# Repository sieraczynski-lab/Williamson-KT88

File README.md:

# Williamson KT88

Lampowy wzmacniacz push-pull w klasycznej topologii Williamsona (wszystkie lampy sterujące na 6SN7), z końcówką na parze KT88 w układzie ultralinearnym (UL). Projekt to wzmacniacz **onyx1944** na jego płytce VA1523:

- wersja na KT88 (zdjęcia, PCB): https://onyx1944.wordpress.com/2023/11/21/williamson-kt88/
- wersja na 6S33S (schemat i zasilacz): https://onyx1944.wordpress.com/2020/03/16/6s33s-williamson-amplifier/

Płytka **VA1523-V1.0** jest kupiona od Onyxa (bez lamp i transformatorów), a Onyx udostępnił schematy. Schemat w tym repozytorium jest przerysowany z jego schematu i **poprawiony według wartości faktycznie wlutowanych na płytce**. Pomarańczowe elementy to te, które trzeba sprawdzić albo dobrać pod toroid TTG-KT88PP i własny transformator sieciowy. Oryginalnych plików Onyxa tu nie ma, to jego praca.

> **Status: płytka w ręku, przed uruchomieniem.** Punkty pracy są szacunkowe (model lampy, Ua ≈ 465 V), do potwierdzenia pomiarem.

> ⚠️ **Wysokie napięcie.** Ua ok. 465 V, a na zimno i przy wysokim napięciu sieci więcej. Kondensatory filtrów rozładowują się przez rezystory 560 k i dzielnik żarzenia; to trwa od kilkudziesięciu sekund do kilku minut. Przed dotknięciem płytki zawsze zmierz napięcie.

## Schematy

| Plik | Zawartość |
|---|---|
| [`schematy/kanal.svg`](schematy/kanal.svg) | Jeden kanał wg VA1523: 6SN7 (wejście + katodyna) → 6SN7 (driver) → 2× KT88 UL, bias osobno dla każdej lampy |
| [`schematy/zasilacz.svg`](schematy/zasilacz.svg) | Zasilacz z płytki (osobno w każdym kanale): mostek, CLC z dławikiem 10 H, Uaa przez R128, bias, podniesienie żarzenia |
| [`schematy/plytka_zasilacza.svg`](schematy/plytka_zasilacza.svg) | Własna płytka zasilacza: bezpieczniki, miękki start K1/K2, opóźnione anody K3/K4 z R_IN, napięcia przemienne do płytki Onyxa, pomiar Ua i dioda HV |
| [`bom/do_zamowienia.csv`](bom/do_zamowienia.csv) | Lista zakupów: zmiany na płytce Onyxa (rezystory 1 %, brakujące R136/R137, kondensatory wejściowe), gniazda, mechanika, przewody, transformatory |
| [`pcb/`](pcb/) | Płytki do zamówienia (KiCad 4 dla EasyEDA Standard, 5 dla EasyEDA Pro i KiCad 8, z klasami sieci): nowy zasilacz 100 × 100 mm, nowa płytka UL/trioda na oba kanały (4 przekaźniki, 100 × 66 mm) oraz z Soloista sterowanie ESP32, przełącznik kolumn, selektor. Połączenia: [`pcb/CZYTAJ_MNIE.txt`](pcb/CZYTAJ_MNIE.txt) |
| [`docs/soloist/`](docs/soloist/) | Opis sterowania i selektora (kopia z Soloista) |
| [`schematy/ul_trioda.svg`](schematy/ul_trioda.svg) | Okablowanie przełącznika UL / trioda: toroid, płytka UL, J101 Onyxa |
| [`schematy/williamson-kt88.html`](schematy/williamson-kt88.html) | Oba schematy z punktami pracy, różnicami płytka/schemat, listą zmian i uruchomieniem (otwórz w przeglądarce) |

## Najważniejsze dane

| | Wartość |
|---|---|
| Lampy | V1, V2: 6SN7 (6N8S); V5, V6: KT88 (lewy kanał; prawy V3, V4, V7, V8) |
| Front end | wejście ok. 4,3 mA / 95 V, katodyna 22k/22k ok. 4,5 mA, driver ok. 5 mA na triodę (bez balansu AC) |
| Końcówka | KT88 UL, Ua ≈ 465 V, 50–55 mA (0,50–0,55 V na 10 Ω), Ug1 ≈ −45…−55 V |
| Transformator wyjściowy | toroidy.pl **TTG-KT88PP** (u Onyxa Hammond 1650HA 6,6 kΩ) |
| Sprzężenie zwrotne | R129 15k z **odczepu 8 Ω** (ok. 12 dB), C123 niemontowany |
| Czułość / moc | ok. 0,65 V / ok. 40 W na kanał, kolumny na odczepie 4 Ω |
| Transformator sieciowy | 400 VA: 360 V (odczepy 345/375 V)/0,65 A, 58 V/100 mA, 6,3 V/8 A, 6,3 V/3 A, ekran ([docs/08](docs/08-zamowienie-toroidy.md)) |
| Dławiki | 2× 10 H / 250 mA / 45 Ω na L106 / L206 |

## Płytka a schemat Onyxa

| Element | Na schemacie | Na płytce |
|---|---|---|
| R117 / R217 | 220k / 1k | **100k / 100k** |
| R124 / R224 | 10 Ω / 470k | **10 Ω / 10 Ω** |
| C123 / C223 | 56 pF | **brak** |
| R101 | 1M | **220k** |
| R103 | 47k | **33k** |
| R104 / C102 | 47 Ω / 47 µF | **zwora / brak** |
| R111, R112 | 470k | **300k** |
| R119, R120 | 470k | **68k** |
| P101, P102 | 47k | **20k** |
| R139, R140 | 47k | **4k7** |
| R129 | 22k | **15k** |
| R134 | 10 Ω | **5,1 Ω** |
| R136 / R137 | 100k / 10k | **brak** w lewym, **300k / 68k** w prawym |
| R130–R133 | 330 Ω | **390 Ω** |
| R143–R152 | 680k | **560k** |
| R125, R126 | 100 Ω | **150 Ω** |
| R141, R142 | 10 Ω / 100 Ω | **47 Ω / 47 Ω** |

## Zasilacz, sterowanie, dodatki i obudowa

Płytka Onyxa dostaje własną, prostą płytkę zasilacza (bez prostowników i filtrów, bo te są na płytce Onyxa): miękki start, opóźnione anody, pomiar Ua. Z [Soloist-KT88](https://github.com/sieraczynski-lab/Soloist-KT88) bierze sterownik ESP32 z automatyczną korektą biasu, układ przełącznika UL / trioda (tu jedna płytka na oba kanały), przełącznik kolumn z triggerem, selektor z drabinką głośności i obudowę. Te płytki Soloista bez zmian w PCB, płytka Onyxa bez cięcia ścieżek. Szczegóły: [docs/09-integracja-soloist.md](docs/09-integracja-soloist.md), obudowa: [`obudowa/`](obudowa/).

## Decyzje i otwarte sprawy

- **Toroid TTG-KT88PP** zamiast Hammonda: sprzężenie zwrotne z odczepu 8 Ω (zbliżona głębokość pętli jak u Onyxa), kolumny na 4 Ω. Kompensację C123 dobrać na oscyloskopie, jeśli prostokąt dzwoni.
- **R128 / R228** (4k7) dobrać do własnego Ua, żeby Uaa wyszło ok. 380–420 V.
- **Driver bez balansu AC:** do V2 dawać 6SN7 o zbliżonych prądach obu triod.
- **Dodatek:** rezystor 100 Ω / 2 W między 4 Ω a COM (wzmacniacz nie pracuje bez obciążenia).
- **Odpowiedzi Onyxa (12.11.2026):** u niego TR1 to toroidy.pl TSTA-0300/001 (300 VA), radzi większy, więc 400 VA jest w porządku. Sprzężenie zwrotne z odczepu 8 Ω (zgodnie z planem). C123 i ewentualnie R102/C101 tylko pod prostokąt (u niego niepotrzebne). Pomyłki na schemacie potwierdzone. Szczegóły w [docs/07](docs/07-wersje-onyxa.md#odpowiedzi-onyxa-12112026).
- **Sprawdzone:** sieć UaFF-L2 (środek żarzenia KT88) to masa (wspólny punkt C108, C126, R142).
- Projekt równoległy: [Soloist-KT88](https://github.com/sieraczynski-lab/Soloist-KT88) (Mullard: EF86 + E88CC LTP + KT88), z podobnym transformatorem sieciowym i tymi samymi toroidami.

## Notatki

1. [Lampy KT88 Psvane: serie i różnice](docs/01-lampy-kt88.md)
2. [Transformatory wyjściowe: Hammond, toroidy.pl, Ogonowski](docs/02-transformatory-wyjsciowe.md)
3. [Topologia: Williamson, Mullard 5-20, 6S33S, 6SN7](docs/03-topologia.md)
4. [Kolumny: impedancja, zwrotnica 2,5-drożna, spadek bafla](docs/04-kolumny.md)
5. [Uruchomienie krok po kroku](docs/05-uruchomienie.md)
6. [Zamawianie płytek PCB](docs/06-pcb.md)
7. [Wersje Onyxa: zdjęcia, schemat i płytka VA1523](docs/07-wersje-onyxa.md)
8. [Specyfikacja do zamówienia w toroidy.pl](docs/08-zamowienie-toroidy.md)
9. [Zasilacz, sterowanie, dodatki i obudowa](docs/09-integracja-soloist.md)
10. [Oprogramowanie ESP32: założenia](docs/10-oprogramowanie-esp32.md)

## Generowanie schematów

Schematy są rysowane skryptem (Python 3, bez dodatkowych bibliotek):

```bash
python3 narzedzia/build.py
```

Obudowa (STEP, DXF, widoki) powstaje z `python3 narzedzia/obudowa/export.py` (wymaga `numpy` i `matplotlib`).

Skrypt [`narzedzia/gen_schemat.py`](narzedzia/gen_schemat.py) zawiera geometrię i wartości elementów. Po zmianie wartości wystarczy uruchomić `build.py` ponownie, a SVG i strona HTML w `schematy/` zostaną odświeżone.

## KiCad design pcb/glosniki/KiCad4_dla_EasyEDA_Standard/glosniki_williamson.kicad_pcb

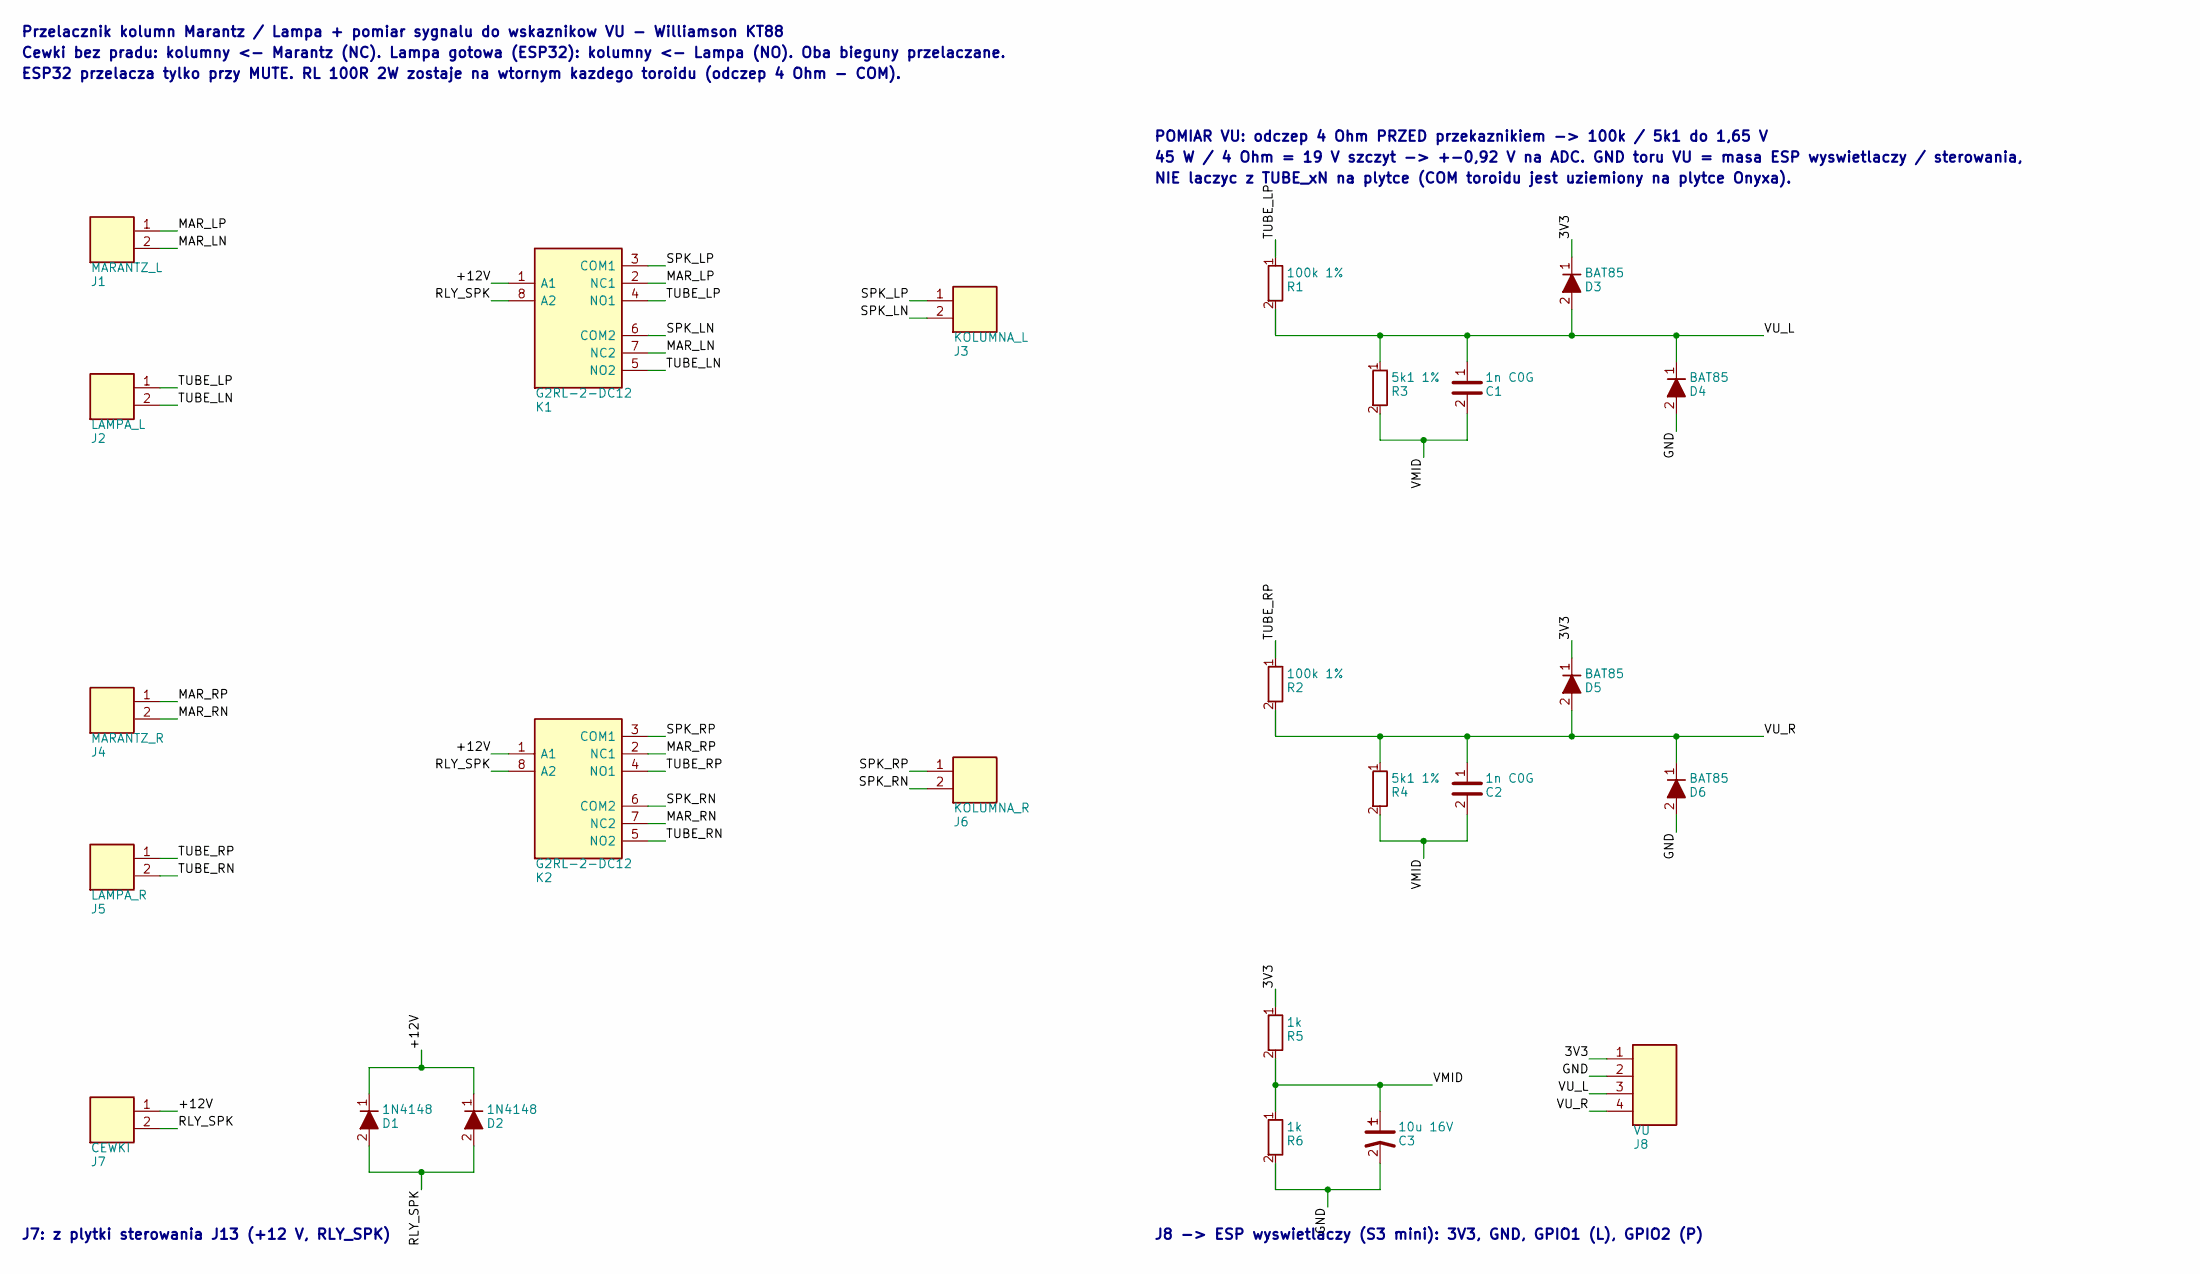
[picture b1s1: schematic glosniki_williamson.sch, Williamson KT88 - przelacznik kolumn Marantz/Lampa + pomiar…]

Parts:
C1, C2: 1n C0G; C_Box_P5_7x4
C3: 10u 16V; CP_Radial_D6.3_P2.5
D1, D2: 1N4148; D_DO-35_P7.62
D3, D4, D5, D6: BAT85; D_DO-35_P7.62_V
J1: MARANTZ_L; TerminalBlock_1x02_P5.08
J2: LAMPA_L; TerminalBlock_1x02_P5.08
J3: KOLUMNA_L; TerminalBlock_1x02_P5.08
J4: MARANTZ_R; TerminalBlock_1x02_P5.08
J5: LAMPA_R; TerminalBlock_1x02_P5.08
J6: KOLUMNA_R; TerminalBlock_1x02_P5.08
J7: CEWKI; PinHeader_1x02_P2.54
J8: VU; PinHeader_1x04_P2.54_H
K1, K2: G2RL-2-DC12; Relay_DPDT_Omron_G2RL
R1, R2: 100k 1%; R_Axial_0.5W_P12.7
R3, R4: 5k1 1%; R_Axial_0.5W_P12.7
R5, R6: 1k; R_Axial_0.5W_P12.7_V

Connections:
3V3: D3.1 (K), D5.1 (K), J8.1, R5.1
+12V: D1.1 (K), D2.1 (K), J7.1, K1.1 (A1), K2.1 (A1)
GND: C3.2, D4.2 (A), D6.2 (A), J8.2, R6.2
MAR_LN: J1.2, K1.7 (NC2)
MAR_LP: J1.1, K1.2 (NC1)
MAR_RN: J4.2, K2.7 (NC2)
MAR_RP: J4.1, K2.2 (NC1)
RLY_SPK: D1.2 (A), D2.2 (A), J7.2, K1.8 (A2), K2.8 (A2)
SPK_LN: J3.2, K1.6 (COM2)
SPK_LP: J3.1, K1.3 (COM1)
SPK_RN: J6.2, K2.6 (COM2)
SPK_RP: J6.1, K2.3 (COM1)
TUBE_LN: J2.2, K1.5 (NO2)
TUBE_LP: J2.1, K1.4 (NO1), R1.1
TUBE_RN: J5.2, K2.5 (NO2)
TUBE_RP: J5.1, K2.4 (NO1), R2.1
VMID: C1.2, C2.2, C3.1, R3.2, R4.2, R5.2, R6.1
VU_L: C1.1, D3.2 (A), D4.1 (K), J8.3, R1.2, R3.1
VU_R: C2.1, D5.2 (A), D6.1 (K), J8.4, R2.2, R4.1

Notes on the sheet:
Przelacznik kolumn Marantz / Lampa + pomiar sygnalu do wskaznikow VU - Williamson KT88
Cewki bez pradu: kolumny <- Marantz (NC). Lampa gotowa (ESP32): kolumny <- Lampa (NO). Oba bieguny przelaczane.
ESP32 przelacza tylko przy MUTE. RL 100R 2W zostaje na wtornym kazdego toroidu (odczep 4 Ohm - COM).
POMIAR VU: odczep 4 Ohm PRZED przekaznikiem -> 100k / 5k1 do 1,65 V
45 W / 4 Ohm = 19 V szczyt -> +-0,92 V na ADC. GND toru VU = masa ESP wyswietlaczy / sterowania,
NIE laczyc z TUBE_xN na plytce (COM toroidu jest uziemiony na plytce Onyxa).
J8 -> ESP wyswietlaczy (S3 mini): 3V3, GND, GPIO1 (L), GPIO2 (P)
J7: z plytki sterowania J13 (+12 V, RLY_SPK)

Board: 2 copper layers, 28 parts (0 on the bottom side), 19 nets, no tracks yet.

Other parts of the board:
MH1, MH2, MH3: M3; MountingHole_M3

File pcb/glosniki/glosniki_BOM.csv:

Oznaczenie;Wartosc;Footprint;Strona;X [mm];Y [mm];Grupa;LCSC;Uwagi
K1;G2RL-2-DC12;Relay_DPDT_Omron_G2RL;GORA;30.00;28.00;PRZEKAZNIKI GLOSNIKOW;C61458;"kanal L: bez pradu cewki kolumna <- Marantz (NC), cewka zasilona: kolumna <- Lampa (NO); + i - przelaczane"
K2;G2RL-2-DC12;Relay_DPDT_Omron_G2RL;GORA;72.00;28.00;PRZEKAZNIKI GLOSNIKOW;C61458;"kanal R: bez pradu cewki kolumna <- Marantz (NC), cewka zasilona: kolumna <- Lampa (NO); + i - przelaczane"
D1;1N4148;D_DO-35_P7.62;GORA;13.00;38.00;PRZEKAZNIKI GLOSNIKOW;;dioda cewki K1
D2;1N4148;D_DO-35_P7.62;GORA;62.00;38.50;PRZEKAZNIKI GLOSNIKOW;;dioda cewki K2
J1;MARANTZ_L;TerminalBlock_1x02_P5.08;GORA;12.00;5.00;ZLACZA;;z wyjscia glosnikowego Marantza, kanal L: 1 +, 2 -
J2;LAMPA_L;TerminalBlock_1x02_P5.08;GORA;27.00;5.00;ZLACZA;;z wtornego T101: 1 odczep 4 Ohm, 2 COM (masa Lampy)
J3;KOLUMNA_L;TerminalBlock_1x02_P5.08;GORA;42.00;5.00;ZLACZA;;do zaciskow kolumny L na tylnej sciance: 1 +, 2 -
J4;MARANTZ_R;TerminalBlock_1x02_P5.08;GORA;58.00;5.00;ZLACZA;;z Marantza, kanal R
J5;LAMPA_R;TerminalBlock_1x02_P5.08;GORA;73.00;5.00;ZLACZA;;z wtornego T201: 1 odczep 4 Ohm, 2 COM
J6;KOLUMNA_R;TerminalBlock_1x02_P5.08;GORA;88.00;5.00;ZLACZA;;do zaciskow kolumny R
J7;CEWKI;PinHeader_1x02_P2.54;GORA;95.50;36.00;ZLACZA;;z plytki sterowania J13
MH1;M3;MountingHole_M3;GORA;4.50;37.50;OTWORY;;
MH2;M3;MountingHole_M3;GORA;51.00;37.50;OTWORY;;
MH3;M3;MountingHole_M3;GORA;95.50;22.00;OTWORY;;

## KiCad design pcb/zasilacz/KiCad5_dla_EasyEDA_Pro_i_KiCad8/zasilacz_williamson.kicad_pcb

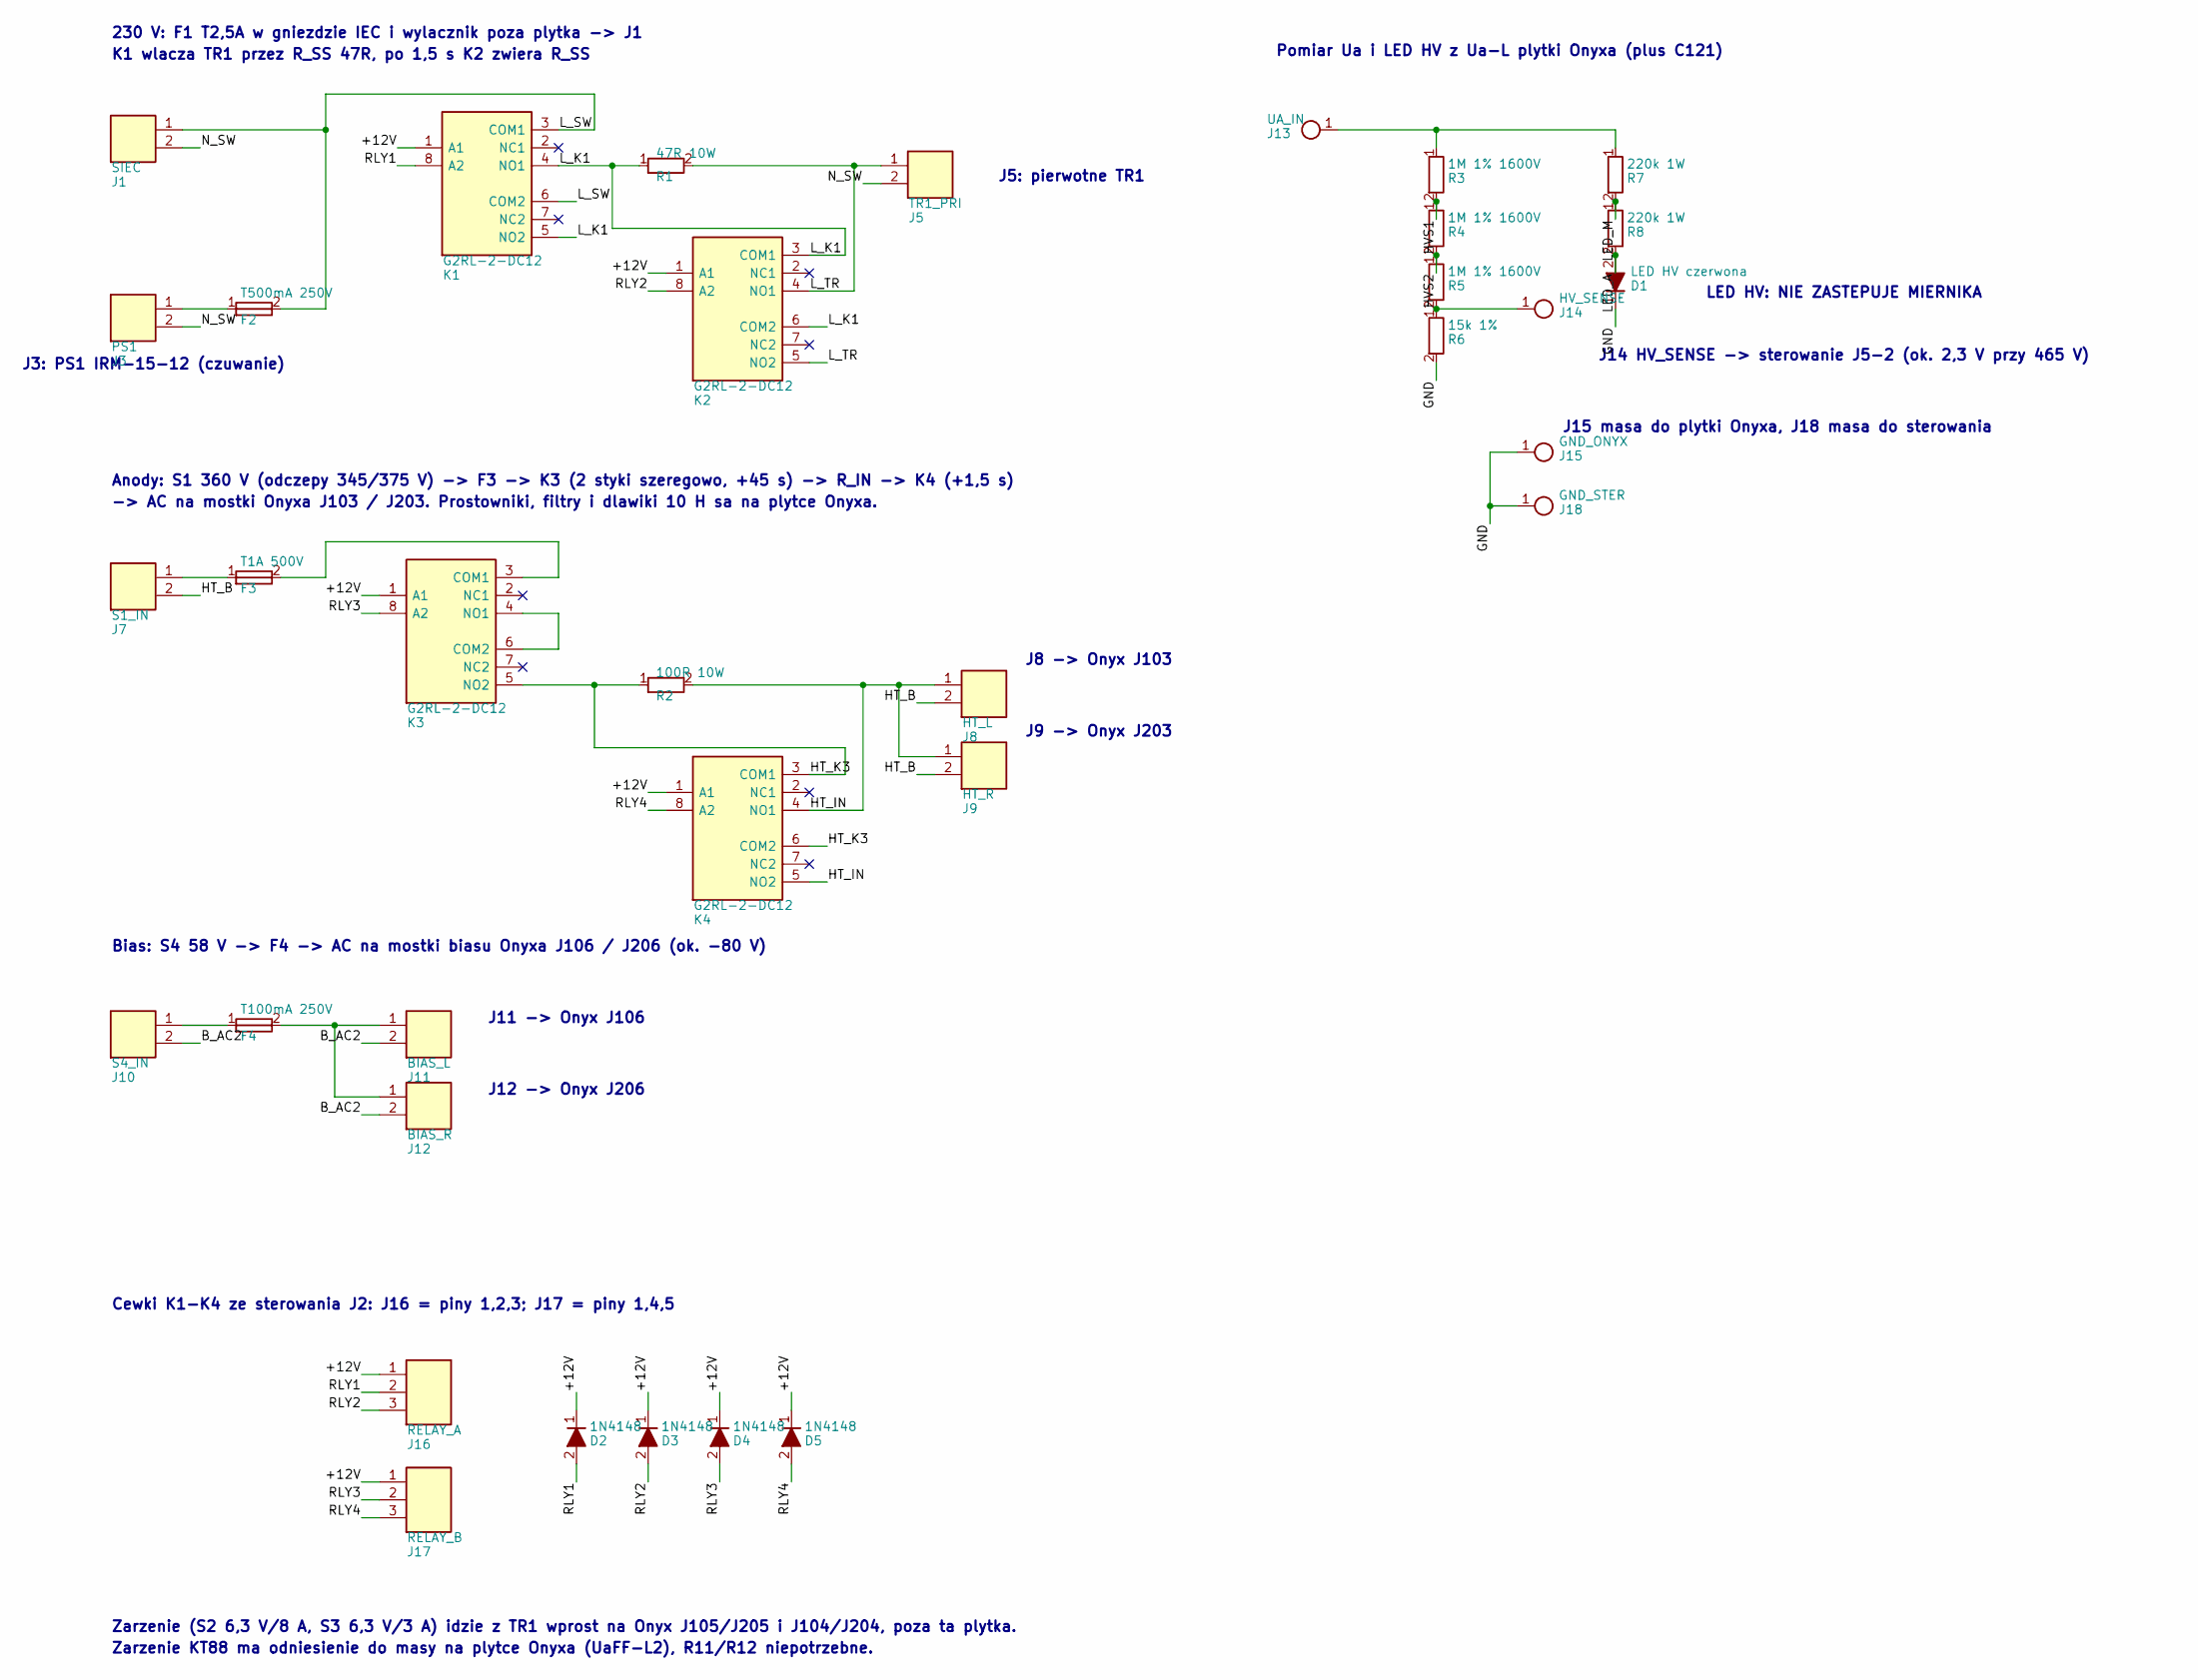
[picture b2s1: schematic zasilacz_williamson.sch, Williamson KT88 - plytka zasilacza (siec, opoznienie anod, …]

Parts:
D1: LED HV czerwona; LED_D3.0_P2.54
D2, D3, D4, D5: 1N4148; D_DO-35_P7.62_V
F2: T500mA 250V; Fuseholder_5x20_Closed_P22.5
F3: T1A 500V; Fuseholder_5x20_Closed_P22.5_V
F4: T100mA 250V; Fuseholder_5x20_Closed_P22.5
J1: SIEC; TerminalBlock_1x02_P5.08_V
J3: PS1; TerminalBlock_1x02_P5.08_V
J5: TR1_PRI; TerminalBlock_1x02_P5.08_V
J7: S1_IN; TerminalBlock_1x02_P7.62_V
J8: HT_L; TerminalBlock_1x02_P7.62_V
J9: HT_R; TerminalBlock_1x02_P7.62_V
J10: S4_IN; TerminalBlock_1x02_P5.08_V
J11: BIAS_L; TerminalBlock_1x02_P5.08
J12: BIAS_R; TerminalBlock_1x02_P5.08
J13: UA_IN; WirePad_4.5
J14: HV_SENSE; WirePad_3.5
J15: GND_ONYX; WirePad_4.5
J16: RELAY_A; PinHeader_1x03_P2.54
J17: RELAY_B; PinHeader_1x03_P2.54
J18: GND_STER; WirePad_3.5
K1, K2, K3, K4: G2RL-2-DC12; Relay_DPDT_Omron_G2RL
R1: 47R 10W; R_Cement_10W_P55.88_V
R2: 100R 10W; R_Cement_10W_P55.88_V
R3, R4, R5: 1M 1% 1600V; R_Axial_1W_P15.24_V
R6: 15k 1%; R_Axial_0.5W_P12.7_V
R7, R8: 220k 1W; R_Axial_1W_P15.24_V

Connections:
+12V: D2.1 (K), D3.1 (K), D4.1 (K), D5.1 (K), J16.1, J17.1, K1.1 (A1), K2.1 (A1), K3.1 (A1), K4.1 (A1)
B_AC1: F4.1, J10.1
B_AC2: J10.2, J11.2, J12.2
B_F: F4.2, J11.1, J12.1
GND: D1.1 (K), J15.1, J18.1, R6.2
HT_B: J7.2, J8.2, J9.2
HT_F: F3.2, K3.3 (COM1)
HT_IN: J8.1, J9.1, K4.4 (NO1), K4.5 (NO2), R2.2
HT_K3: K3.5 (NO2), K4.3 (COM1), K4.6 (COM2), R2.1
HT_TR: F3.1, J7.1
HVS1: R3.2, R4.1
HVS2: R4.2, R5.1
HV_SENSE: J14.1, R5.2, R6.1
K3_MID: K3.4 (NO1), K3.6 (COM2)
LED_A: D1.2 (A), R8.2
LED_M: R7.2, R8.1
L_K1: K1.4 (NO1), K1.5 (NO2), K2.3 (COM1), K2.6 (COM2), R1.1
L_SW: F2.2, J1.1, K1.3 (COM1), K1.6 (COM2)
L_TR: J5.1, K2.4 (NO1), K2.5 (NO2), R1.2
L_TR2: F2.1, J3.1
N_SW: J1.2, J3.2, J5.2
RLY1: D2.2 (A), J16.2, K1.8 (A2)
RLY2: D3.2 (A), J16.3, K2.8 (A2)
RLY3: D4.2 (A), J17.2, K3.8 (A2)
RLY4: D5.2 (A), J17.3, K4.8 (A2)
UA: J13.1, R3.1, R7.1

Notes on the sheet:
230 V: F1 T2,5A w gniezdzie IEC i wylacznik poza plytka -> J1
K1 wlacza TR1 przez R_SS 47R, po 1,5 s K2 zwiera R_SS
J5: pierwotne TR1
J3: PS1 IRM-15-12 (czuwanie)
Anody: S1 360 V (odczepy 345/375 V) -> F3 -> K3 (2 styki szeregowo, +45 s) -> R_IN -> K4 (+1,5 s)
-> AC na mostki Onyxa J103 / J203. Prostowniki, filtry i dlawiki 10 H sa na plytce Onyxa.
J8 -> Onyx J103
J9 -> Onyx J203
Bias: S4 58 V -> F4 -> AC na mostki biasu Onyxa J106 / J206 (ok. -80 V)
J11 -> Onyx J106
J12 -> Onyx J206
Pomiar Ua i LED HV z Ua-L plytki Onyxa (plus C121)
J14 HV_SENSE -> sterowanie J5-2 (ok. 2,3 V przy 465 V)
J15 masa do plytki Onyxa, J18 masa do sterowania
LED HV: NIE ZASTEPUJE MIERNIKA
Cewki K1-K4 ze sterowania J2: J16 = piny 1,2,3; J17 = piny 1,4,5
Zarzenie (S2 6,3 V/8 A, S3 6,3 V/3 A) idzie z TR1 wprost na Onyx J105/J205 i J104/J204, poza ta plytka.
Zarzenie KT88 ma odniesienie do masy na plytce Onyxa (UaFF-L2), R11/R12 niepotrzebne.

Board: 2 copper layers, 39 parts (0 on the bottom side), 26 nets, no tracks yet.

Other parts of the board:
MH1, MH2, MH3, MH4: M3; MountingHole_M3

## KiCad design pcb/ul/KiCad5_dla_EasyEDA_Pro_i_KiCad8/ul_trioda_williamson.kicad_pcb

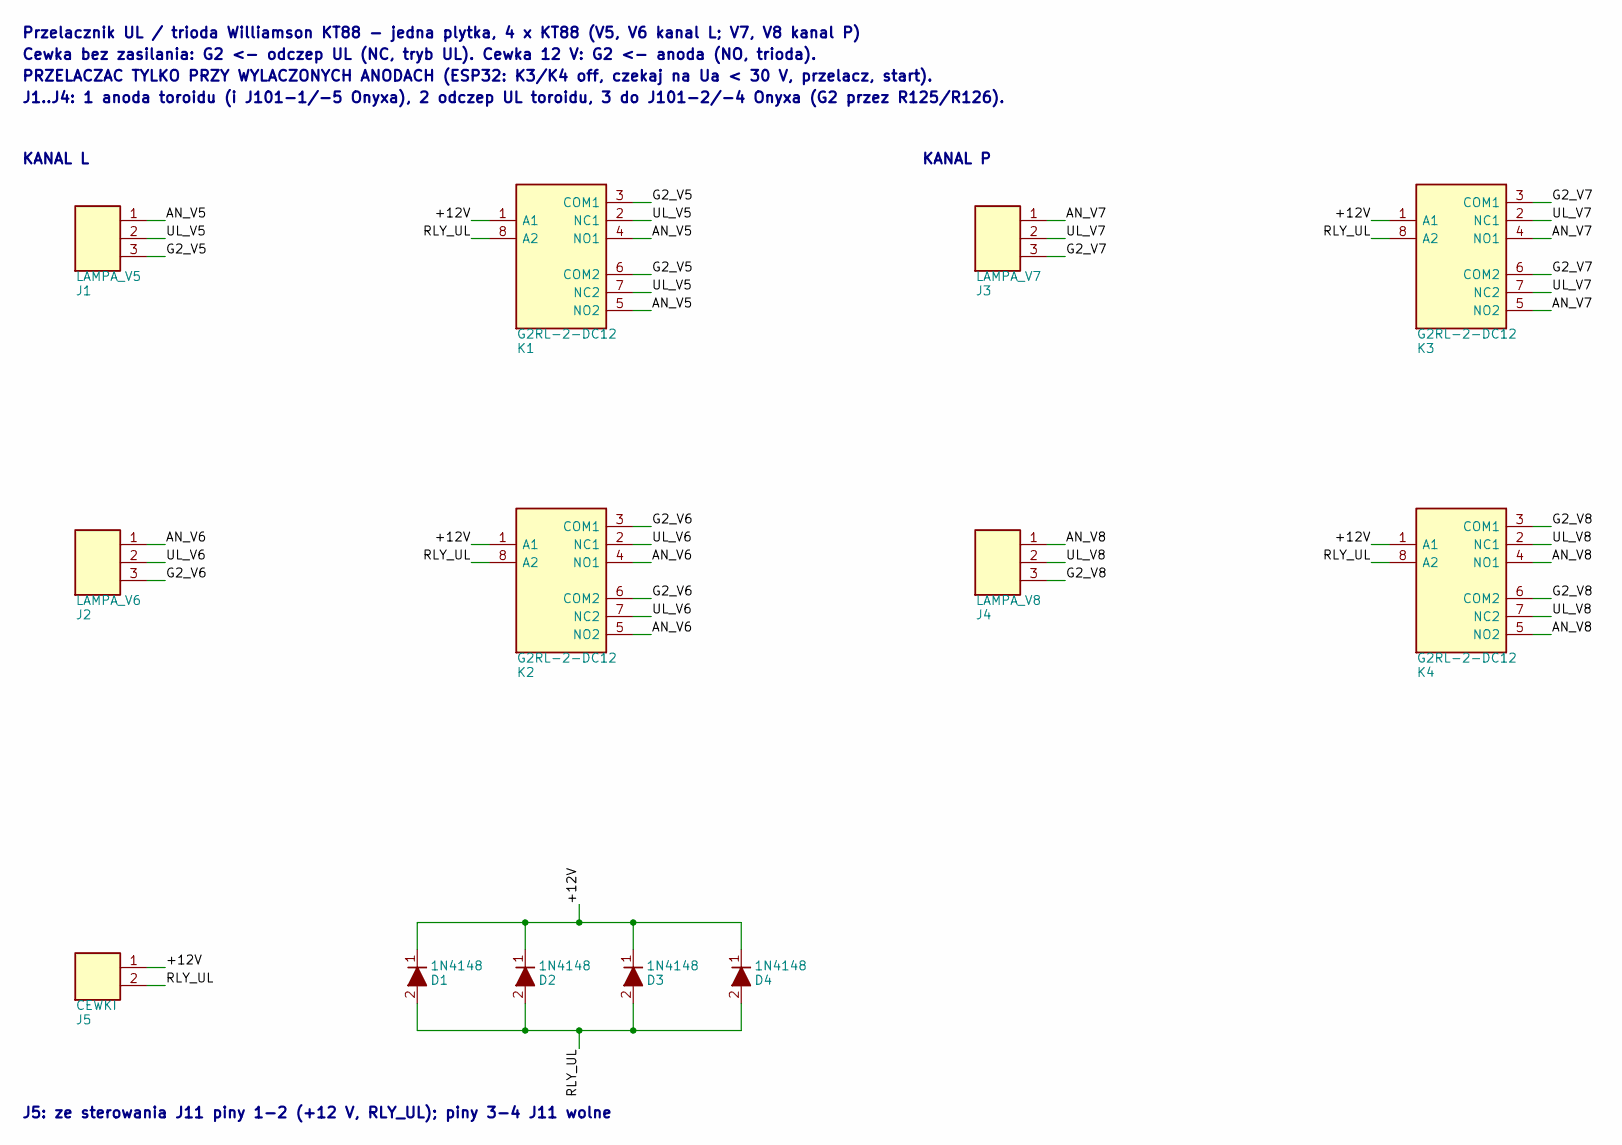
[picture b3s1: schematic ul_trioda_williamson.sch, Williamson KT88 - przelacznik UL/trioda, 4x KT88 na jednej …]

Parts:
D1, D2, D3, D4: 1N4148; D_DO-35_P7.62
J1: LAMPA_V5; TerminalBlock_1x03_P7.62_V
J2: LAMPA_V6; TerminalBlock_1x03_P7.62_V
J3: LAMPA_V7; TerminalBlock_1x03_P7.62_V
J4: LAMPA_V8; TerminalBlock_1x03_P7.62_V
J5: CEWKI; TerminalBlock_1x02_P5.08
K1, K2, K3, K4: G2RL-2-DC12; Relay_DPDT_Omron_G2RL

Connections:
+12V: D1.1 (K), D2.1 (K), D3.1 (K), D4.1 (K), J5.1, K1.1 (A1), K2.1 (A1), K3.1 (A1), K4.1 (A1)
AN_V5: J1.1, K1.4 (NO1), K1.5 (NO2)
AN_V6: J2.1, K2.4 (NO1), K2.5 (NO2)
AN_V7: J3.1, K3.4 (NO1), K3.5 (NO2)
AN_V8: J4.1, K4.4 (NO1), K4.5 (NO2)
G2_V5: J1.3, K1.3 (COM1), K1.6 (COM2)
G2_V6: J2.3, K2.3 (COM1), K2.6 (COM2)
G2_V7: J3.3, K3.3 (COM1), K3.6 (COM2)
G2_V8: J4.3, K4.3 (COM1), K4.6 (COM2)
RLY_UL: D1.2 (A), D2.2 (A), D3.2 (A), D4.2 (A), J5.2, K1.8 (A2), K2.8 (A2), K3.8 (A2), K4.8 (A2)
UL_V5: J1.2, K1.2 (NC1), K1.7 (NC2)
UL_V6: J2.2, K2.2 (NC1), K2.7 (NC2)
UL_V7: J3.2, K3.2 (NC1), K3.7 (NC2)
UL_V8: J4.2, K4.2 (NC1), K4.7 (NC2)

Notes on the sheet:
Przelacznik UL / trioda Williamson KT88 - jedna plytka, 4 x KT88 (V5, V6 kanal L; V7, V8 kanal P)
Cewka bez zasilania: G2 <- odczep UL (NC, tryb UL). Cewka 12 V: G2 <- anoda (NO, trioda).
PRZELACZAC TYLKO PRZY WYLACZONYCH ANODACH (ESP32: K3/K4 off, czekaj na Ua < 30 V, przelacz, start).
J1..J4: 1 anoda toroidu (i J101-1/-5 Onyxa), 2 odczep UL toroidu, 3 do J101-2/-4 Onyxa (G2 przez R125/R126).
KANAL L
KANAL P
J5: ze sterowania J11 piny 1-2 (+12 V, RLY_UL); piny 3-4 J11 wolne

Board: 2 copper layers, 17 parts (0 on the bottom side), 14 nets, no tracks yet.

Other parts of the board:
MH1, MH2, MH3, MH4: M3; MountingHole_M3
